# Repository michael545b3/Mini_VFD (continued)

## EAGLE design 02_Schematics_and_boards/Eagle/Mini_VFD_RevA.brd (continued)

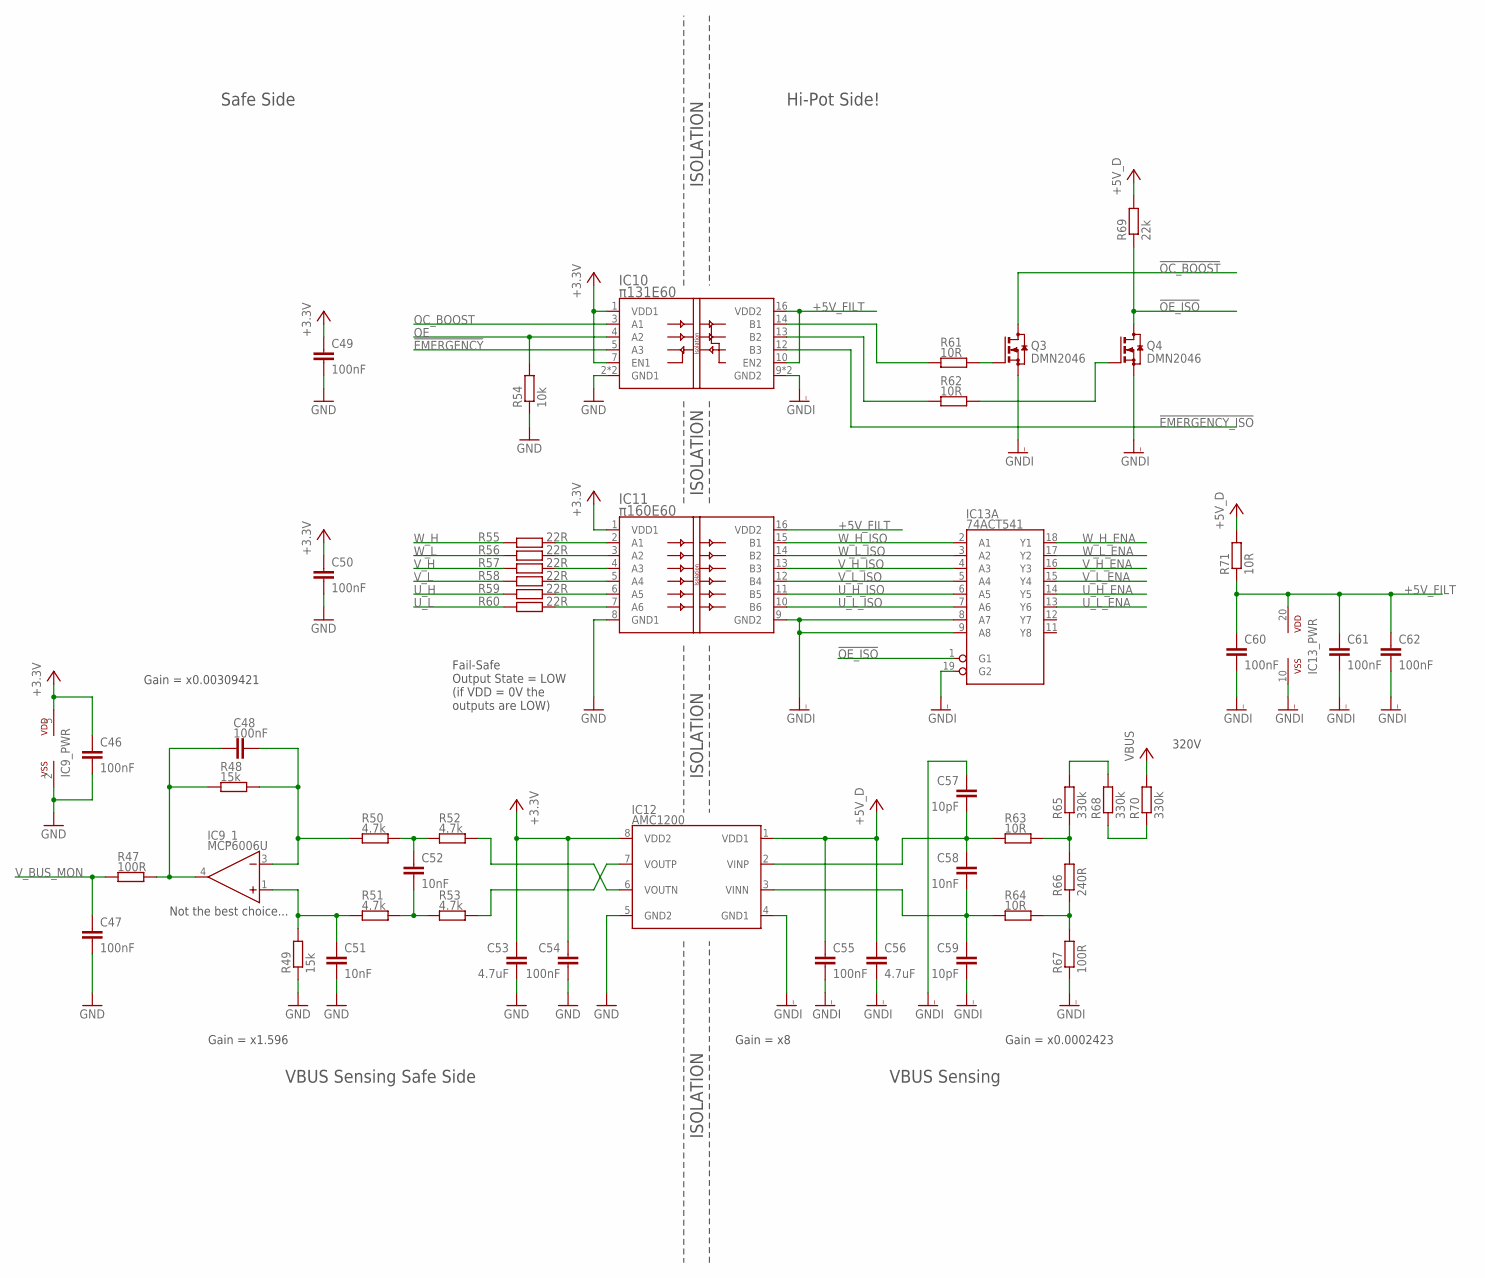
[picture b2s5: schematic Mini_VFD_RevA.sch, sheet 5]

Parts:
C46, C47, C48, C49, C50, C54, C55, C60, C61, C62: 100nF; C0603
C51, C52, C58: 10nF; C0603
C53, C56: 4.7uF; C0603
C57, C59: 10pF; C0603
IC9: MCP6006U; SOT23-5
IC10: π131E60; SOIC16R
IC11: π160E60; SOIC16R
IC12: AMC1200; SOIC8_W
IC13: 74ACT541; SOIC20NS
Q3, Q4: DMN2046; SOT23
R47, R67: 100R; R0603
R48, R49: 15k; R0603
R50, R51, R52, R53: 4.7k; R0603
R54: 10k; R0603
R55, R56, R57, R58, R59, R60: 22R; R0603
R61, R62, R63, R64, R71: 10R; R0603
R65, R68, R70: 330k; R1206
R66: 240R; R0603
R69: 22k; R0603

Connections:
!EMERGENCY: IC10.5 (A3); also elsewhere on the board
!EMERGENCY_ISO: IC10.12 (B3); also elsewhere on the board
!OC_BOOST: Q3.3 (D); also elsewhere on the board
!OE_ISO: IC13.1 (G1), Q4.3 (D), R69.1
+3.3V: C46.1, C49.1, C50.1, C53.1, C54.1, IC9.5 (VDD), IC10.1 (VDD1), IC10.7 (EN1), IC11.1 (VDD1), IC12.8 (VDD2); also elsewhere on the board
+5V_D: C55.1, C56.1, IC12.1 (VDD1), R69.2, R71.2; also elsewhere on the board
+5V_FILT: C60.1, C61.1, C62.1, IC10.10 (EN2), IC10.16 (VDD2), IC11.16 (VDD2), IC13.20 (VDD), R71.1
GND: C46.2, C47.2, C49.2, C50.2, C51.2, C53.2, C54.2, IC9.2 (VSS), IC10.2 (GND1), IC10.8 (GND1), IC11.8 (GND1), IC12.5 (GND2), R49.1, R54.1; also elsewhere on the board
GNDI: C55.2, C56.2, C57.1, C59.2, C60.2, C61.2, C62.2, IC10.9 (GND2), IC10.15 (GND2), IC11.9 (GND2), IC12.4 (GND1), IC13.8 (A7), IC13.9 (A8), IC13.10 (VSS), IC13.19 (G2), Q3.2 (S), Q4.2 (S), R67.1; also elsewhere on the board
unnamed: Q3.1 (G), R61.2
unnamed: IC12.6 (VOUTN), R52.1
unnamed: IC11.2 (A1), R55.2
unnamed: IC11.3 (A2), R56.2
unnamed: IC11.4 (A3), R57.2
unnamed: IC10.14 (B1), R61.1
unnamed: R64.1, R66.1, R67.2
unnamed: IC11.5 (A4), R58.2
unnamed: IC10.13 (B2), R62.1
unnamed: IC11.6 (A5), R59.2
unnamed: IC11.7 (A6), R60.2
unnamed: Q4.1 (G), R62.2
unnamed: R68.1, R70.1
unnamed: R65.2, R68.2
unnamed: IC12.7 (VOUTP), R53.1
unnamed: C52.1, R50.1, R52.2
unnamed: C52.2, R51.1, R53.2
unnamed: C48.2, IC9.3 (-IN), R48.1, R50.2
unnamed: C51.1, IC9.1 (+IN), R49.2, R51.2
unnamed: C48.1, IC9.4 (OUT), R47.1, R48.2
OC_BOOST: IC10.3 (A1); also elsewhere on the board
OE: IC10.4 (A2), R54.2; also elsewhere on the board
U_H: R59.1; also elsewhere on the board
U_H_ENA: IC13.14 (Y5); also elsewhere on the board
U_H_ISO: IC11.11 (B5), IC13.6 (A5)
U_L: R60.1; also elsewhere on the board
U_L_ENA: IC13.13 (Y6); also elsewhere on the board
U_L_ISO: IC11.10 (B6), IC13.7 (A6)
VBUS: R70.2; also elsewhere on the board
VBUS_MON: C57.2, C58.1, IC12.2 (VINP), R63.2
VBUS_MON_ATT: R63.1, R65.1, R66.2
VBUS_MON_NEG: C58.2, C59.1, IC12.3 (VINN), R64.2
V_BUS_MON: C47.1, R47.2; also elsewhere on the board
V_H: R57.1; also elsewhere on the board
V_H_ENA: IC13.16 (Y3); also elsewhere on the board
V_H_ISO: IC11.13 (B3), IC13.4 (A3)
V_L: R58.1; also elsewhere on the board
V_L_ENA: IC13.15 (Y4); also elsewhere on the board
V_L_ISO: IC11.12 (B4), IC13.5 (A4)
W_H: R55.1; also elsewhere on the board
W_H_ENA: IC13.18 (Y1); also elsewhere on the board
W_H_ISO: IC11.15 (B1), IC13.2 (A1)
W_L: R56.1; also elsewhere on the board
W_L_ENA: IC13.17 (Y2); also elsewhere on the board
W_L_ISO: IC11.14 (B2), IC13.3 (A2)

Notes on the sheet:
Fail-Safe Output State = LOW (if VDD = 0V the outputs are LOW)
ISOLATION
Gain = x8
320V
Gain = x0.0002423
Safe Side
Hi-Pot Side!
VBUS Sensing
VBUS Sensing Safe Side
Not the best choice...
Gain = x1.596
Gain = x0.00309421

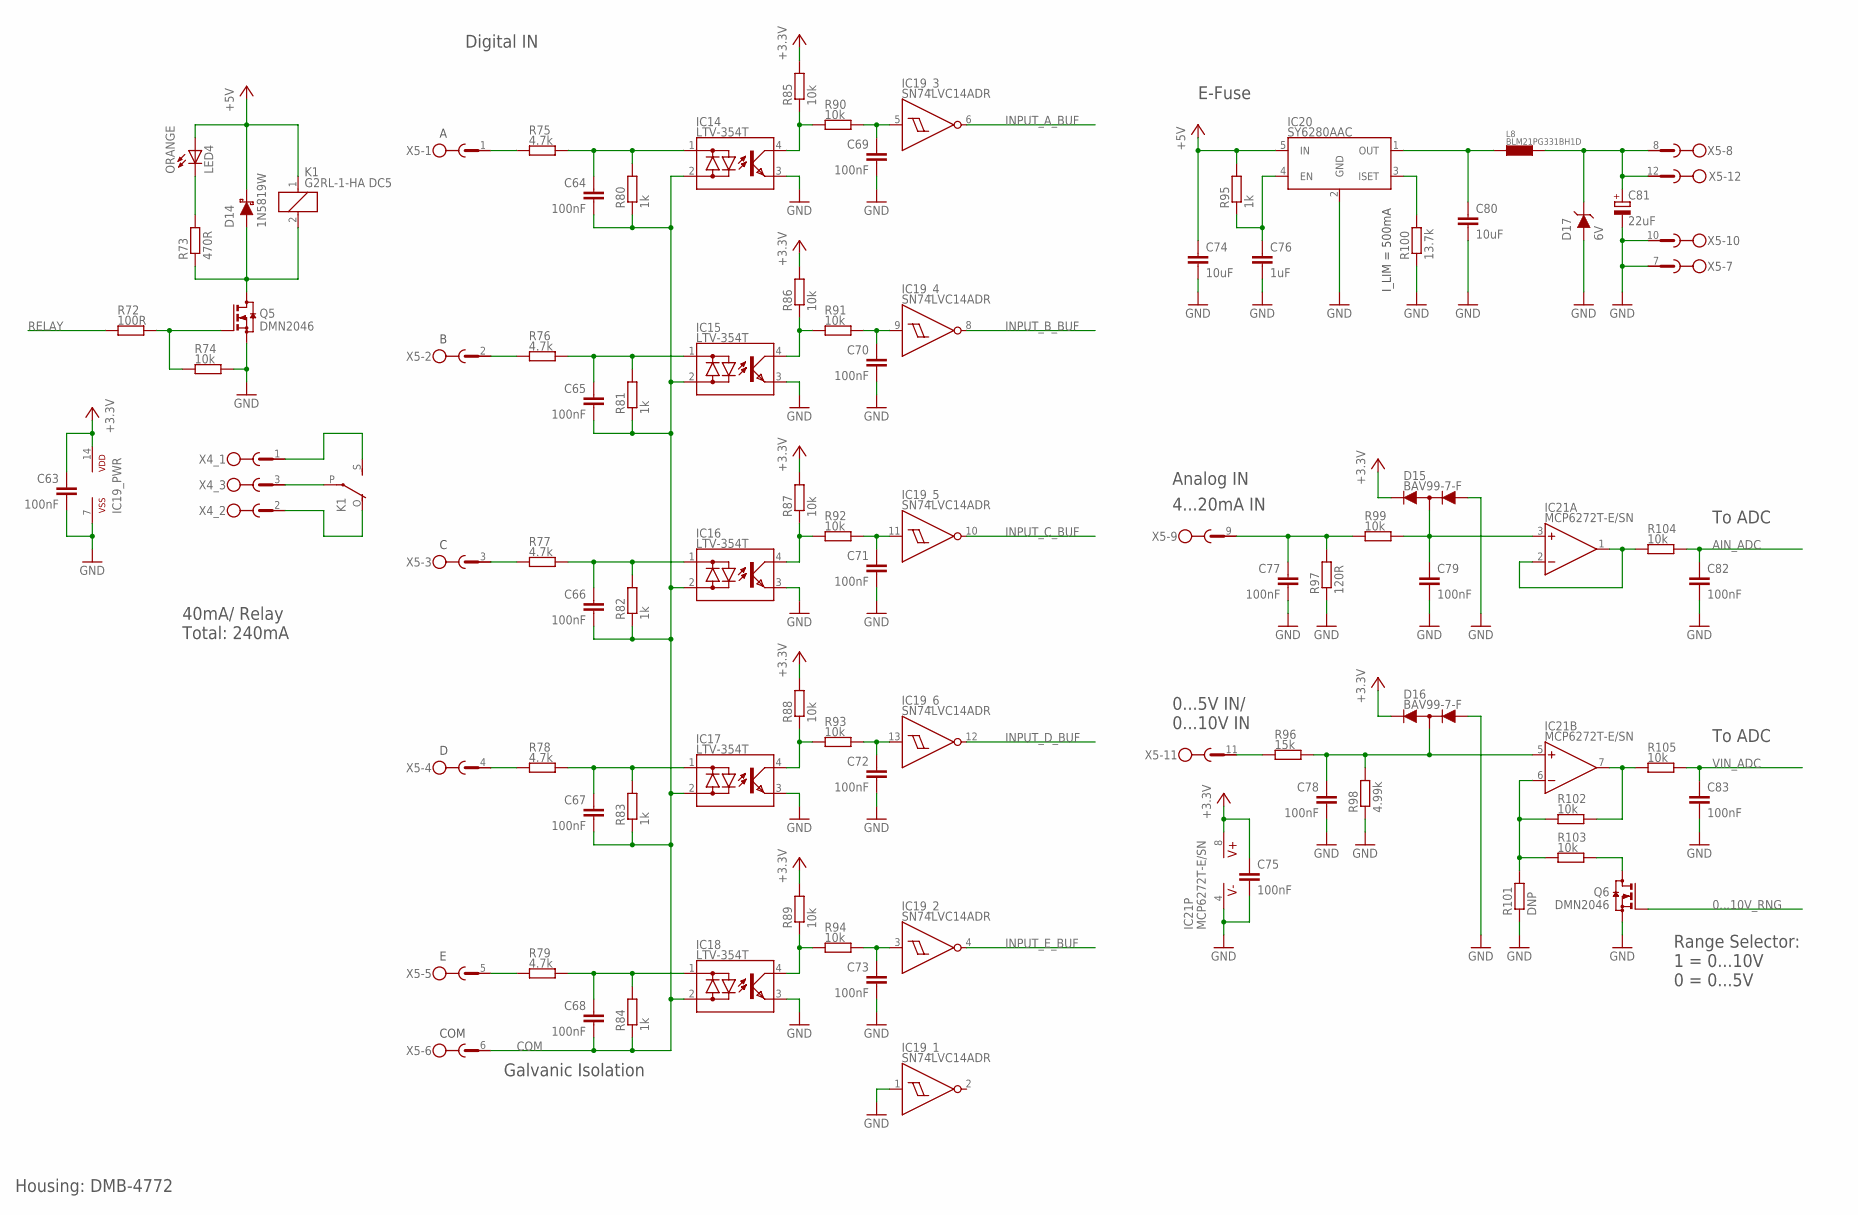
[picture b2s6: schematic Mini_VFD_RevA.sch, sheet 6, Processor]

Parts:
C63, C64, C65, C66, C67, C68, C69, C70, C71, C72, C73, C75, C77, C78, C79, C82, C83: 100nF; C0603
C74, C80: 10uF; C0805
C76: 1uF; C0603
C81: 22uF; E2-5
D14: 1N5819W; SOD123
D15, D16: BAV99-7-F; SOT23
D17: 6V; DO214AC
IC14, IC15, IC16, IC17, IC18: LTV-354T; SOP04
IC19: SN74LVC14ADR; SO14
IC20: SY6280AAC; SOT23-5
IC21: MCP6272T-E/SN; SO08
K1: G2RL-1-HA DC5; E3206S
L8: BLM21PG331BH1D; R0805
LED4: ORANGE; LED_0603
Q5, Q6: DMN2046; SOT23
R72: 100R; R0603
R73: 470R; R0603
R74, R85, R86, R87, R88, R89, R90, R91, R92, R93, R94, R99, R102, R103, R104, R105: 10k; R0603
R75, R76, R77, R78, R79: 4.7k; R0805
R80, R81, R82, R83, R84, R95: 1k; R0603
R96: 15k; R0603
R97: 120R; R1206
R98: 4.99k; R0603
R100: 13.7k; R0603
R101: DNP; R0603
X4: MSTBV3
X5: MSTBV12

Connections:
0...10V_RNG: Q6.1 (G); also elsewhere on the board
!INPUT_A: IC14.4 (C), R85.1, R90.1
!INPUT_A_FILT: C69.1, IC19.5 (I), R90.2
!INPUT_B: IC15.4 (C), R86.1, R91.1
!INPUT_B_FILT: C70.1, IC19.9 (I), R91.2
!INPUT_C: IC16.4 (C), R87.1, R92.1
!INPUT_C_FILT: C71.1, IC19.11 (I), R92.2
!INPUT_D: IC17.4 (C), R88.1, R93.1
!INPUT_D_FILT: C72.1, IC19.13 (I), R93.2
!INPUT_E: IC18.4 (C), R89.1, R94.1
!INPUT_E_FILT: C73.1, IC19.3 (I), R94.2
+3.3V: C63.1, C75.1, D15.2 (C), D16.2 (C), IC19.14 (VDD), IC21.8 (V+), R85.2, R86.2, R87.2, R88.2, R89.2; also elsewhere on the board
+5V: C74.1, D14.1 (C), IC20.5 (IN), K1.1, LED4.A, R95.2; also elsewhere on the board
+5V_OUT: C81.+, D17.C, L8.2, X5.8, X5.12
AIN_ADC: C82.1, R104.2; also elsewhere on the board
COM: C64.2, C65.2, C66.2, C67.2, C68.2, IC14.2 (AC2), IC15.2 (AC2), IC16.2 (AC2), IC17.2 (AC2), IC18.2 (AC2), R80.1, R81.1, R82.1, R83.1, R84.1, X5.6
GND: C63.2, C69.2, C70.2, C71.2, C72.2, C73.2, C74.2, C75.2, C76.2, C77.2, C78.2, C79.2, C80.2, C81.-, C82.2, C83.2, D15.1 (A), D16.1 (A), D17.A, IC14.3 (E), IC15.3 (E), IC16.3 (E), IC17.3 (E), IC18.3 (E), IC19.1 (I), IC19.7 (VSS), IC20.2 (GND), IC21.4 (V-), Q5.2 (S), Q6.2 (S), R74.2, R97.1, R98.1, R100.1, R101.1, X5.7, X5.10; also elsewhere on the board
INPUT_A_BUF: IC19.6 (O); also elsewhere on the board
INPUT_B_BUF: IC19.8 (O); also elsewhere on the board
INPUT_C_BUF: IC19.10 (O); also elsewhere on the board
INPUT_D_BUF: IC19.12 (O); also elsewhere on the board
INPUT_E_BUF: IC19.4 (O); also elsewhere on the board
IN_A: R75.1, X5.1
IN_A_OPTO: C64.1, IC14.1 (AC1), R75.2, R80.2
IN_B: R76.1, X5.2
IN_B_OPTO: C65.1, IC15.1 (AC1), R76.2, R81.2
IN_C: R77.1, X5.3
IN_C_OPTO: C66.1, IC16.1 (AC1), R77.2, R82.2
IN_D: R78.1, X5.4
IN_D_OPTO: C67.1, IC17.1 (AC1), R78.2, R83.2
IN_E: R79.1, X5.5
IN_E_OPTO: C68.1, IC18.1 (AC1), R79.2, R84.2
unnamed: LED4.C, R73.2
unnamed: C77.1, R97.2, R99.1, X5.9
unnamed: IC20.3 (ISET), R100.2
unnamed: C79.1, D15.3 (AC), IC21.3 (+IN), R99.2
unnamed: C76.1, IC20.4 (EN), R95.1
unnamed: IC21.1 (OUT), IC21.2 (-IN), R104.1
unnamed: C78.1, D16.3 (AC), IC21.5 (+IN), R96.2, R98.2
unnamed: R96.1, X5.11
unnamed: IC21.7 (OUT), R102.2, R105.1
unnamed: IC21.6 (-IN), R101.2, R102.1, R103.2
unnamed: Q6.3 (D), R103.1
unnamed: C80.1, IC20.1 (OUT), L8.1
unnamed: K1.P, X4.3
unnamed: K1.O, X4.2
unnamed: K1.S, X4.1
RELAY: R72.1; also elsewhere on the board
RELAY_DRAIN: D14.2 (A), K1.2, Q5.3 (D), R73.1
RELAY_R: Q5.1 (G), R72.2, R74.1
VIN_ADC: C83.1, R105.2; also elsewhere on the board

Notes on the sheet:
Housing: DMB-4772
40mA/ Relay Total: 240mA
I_LIM = 500mA
COM
Digital IN
Analog IN
4...20mA IN
0...5V IN/ 0...10V IN
Range Selector: 1 = 0...10V 0 = 0...5V
To ADC
Galvanic Isolation
E-Fuse

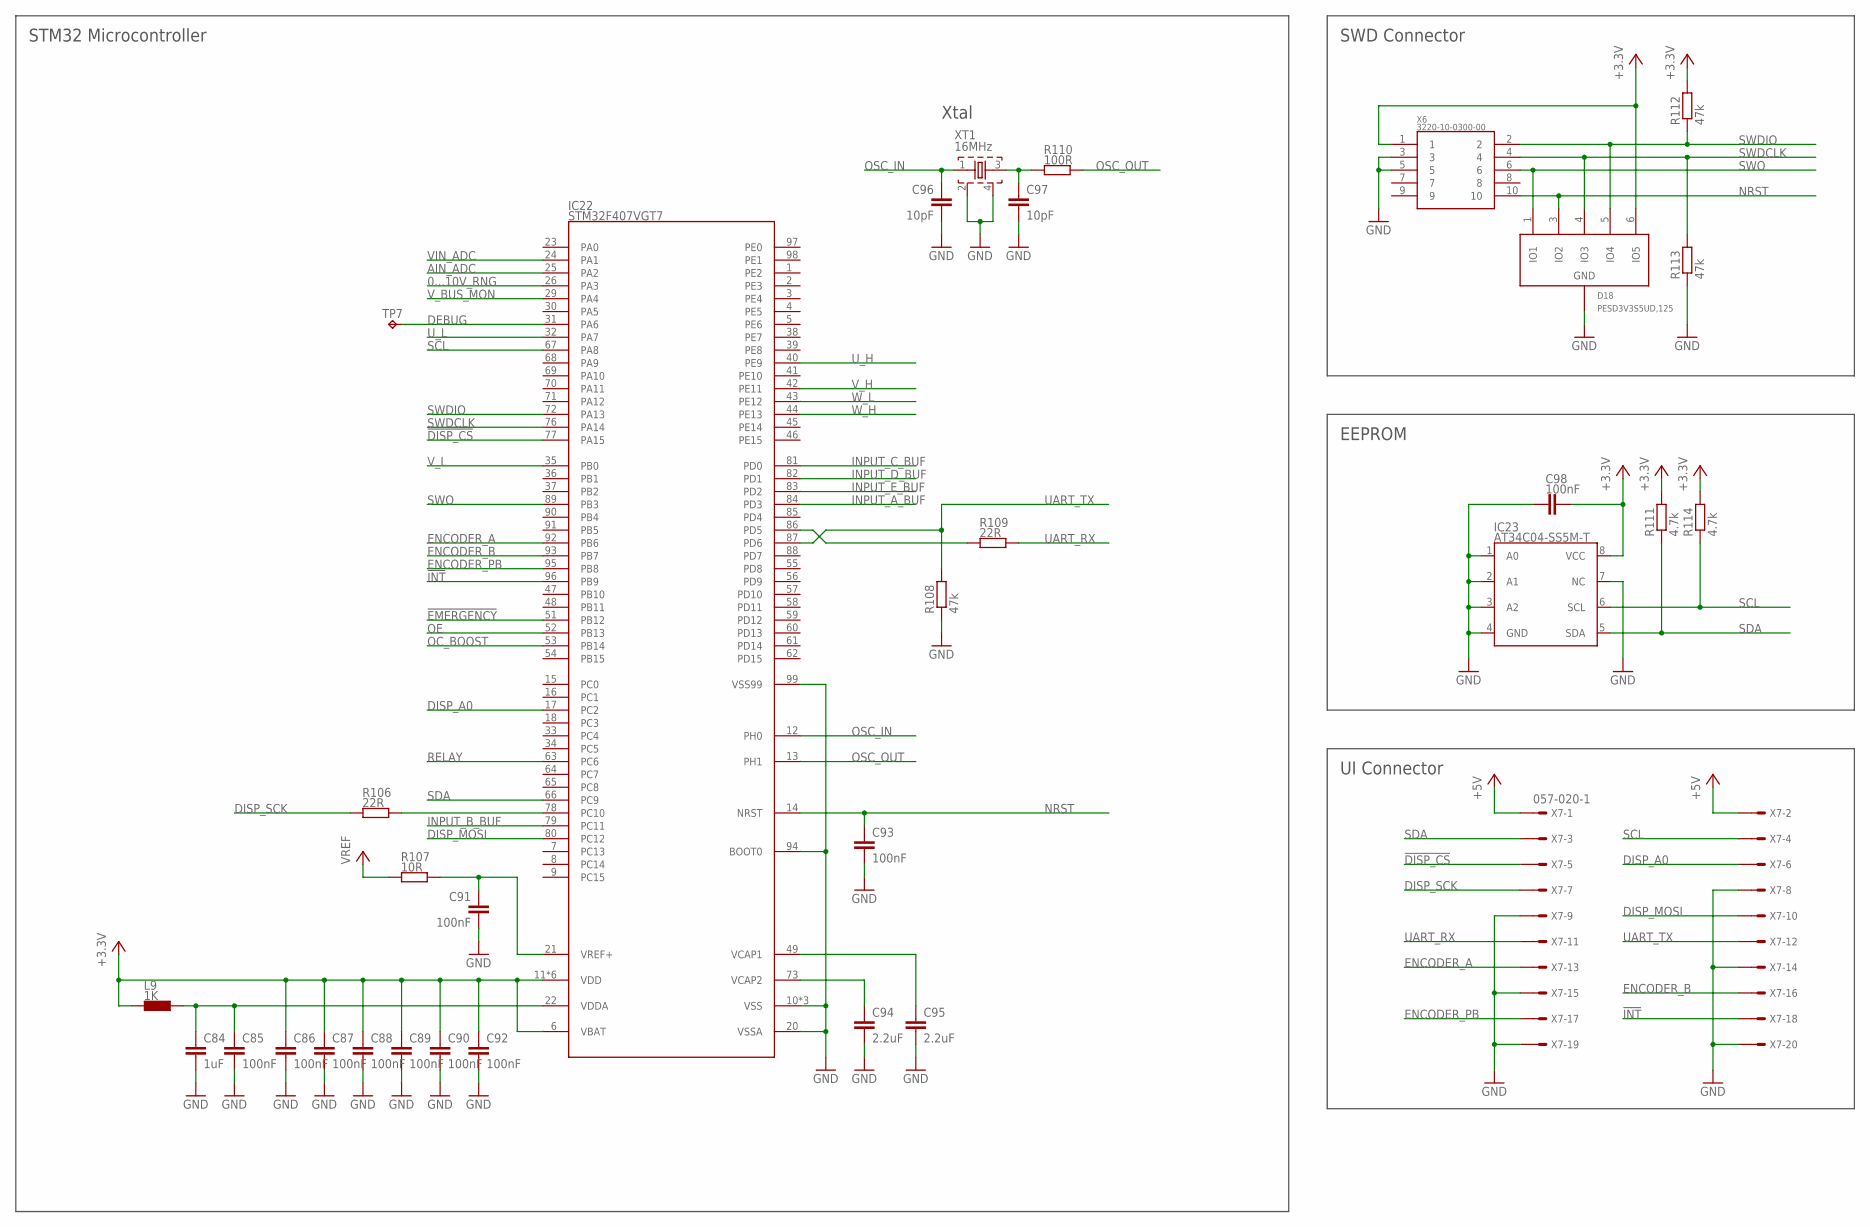
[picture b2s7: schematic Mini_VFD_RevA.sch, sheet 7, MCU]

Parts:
C84: 1uF; C0603
C85, C86, C87, C88, C89, C90, C91, C92, C93, C98: 100nF; C0603
C94, C95: 2.2uF; C0603
C96, C97: 10pF; C0603
D18: PESD3V3S5UD,125; TSOP-6
IC22: STM32F407VGT7; LQFP100
IC23: AT34C04-SS5M-T; SOIC8
L9: 1K; R0603
R106, R109: 22R; R0603
R107: 10R; R0603
R108, R112, R113: 47k; R0603
R110: 100R; R0603
R111, R114: 4.7k; R0603
TP7: TP_SOLDREYE; SOLDER_EYE
X6: 3220-10-0300-00
X7: 057-020-1
XT1: 16MHz; 3225_4P

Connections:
0...10V_RNG: IC22.26 (PA3); also elsewhere on the board
!DISP_CS: IC22.77 (PA15), X7.5
!EMERGENCY: IC22.51 (PB12); also elsewhere on the board
!INT: IC22.96 (PB9), X7.18
+3.3V: C86.1, C87.1, C88.1, C89.1, C90.1, C92.1, C98.2, D18.6 (IO5), IC22.6 (VBAT), IC22.11 (VDD), IC22.19 (VDD), IC22.28 (VDD), IC22.50 (VDD), IC22.75 (VDD), IC22.100 (VDD), IC23.8 (VCC), L9.2, R111.2, R112.2, R114.2, X6.1; also elsewhere on the board
+3.3V_FILT: C84.1, C85.1, IC22.22 (VDDA), L9.1
+5V: X7.1, X7.2; also elsewhere on the board
AIN_ADC: IC22.25 (PA2); also elsewhere on the board
DEBUG: IC22.31 (PA6), TP7.1
DISP_A0: IC22.17 (PC2), X7.6
DISP_MOSI: IC22.80 (PC12), X7.10
DISP_SCK: R106.1, X7.7
ENCODER_A: IC22.92 (PB6), X7.13
ENCODER_B: IC22.93 (PB7), X7.16
ENCODER_PB: IC22.95 (PB8), X7.17
GND: C84.2, C85.2, C86.2, C87.2, C88.2, C89.2, C90.2, C91.2, C92.2, C93.2, C94.2, C95.2, C96.2, C97.2, C98.1, D18.2 (GND), IC22.10 (VSS), IC22.20 (VSSA), IC22.27 (VSS), IC22.74 (VSS), IC22.94 (BOOT0), IC22.99 (VSS99), IC23.1 (A0), IC23.2 (A1), IC23.3 (A2), IC23.4 (GND), IC23.7 (NC), R108.1, R113.1, X6.3, X6.5, X7.8, X7.9, X7.14, X7.15, X7.19, X7.20, XT1.2, XT1.4; also elsewhere on the board
INPUT_A_BUF: IC22.84 (PD3); also elsewhere on the board
INPUT_B_BUF: IC22.79 (PC11); also elsewhere on the board
INPUT_C_BUF: IC22.81 (PD0); also elsewhere on the board
INPUT_D_BUF: IC22.82 (PD1); also elsewhere on the board
INPUT_E_BUF: IC22.83 (PD2); also elsewhere on the board
unnamed: IC22.78 (PC10), R106.2
unnamed: IC22.86 (PD5), R109.1
unnamed: C94.1, IC22.73 (VCAP2)
unnamed: C95.1, IC22.49 (VCAP1)
unnamed: C97.1, R110.1, XT1.3
unnamed: C91.1, IC22.21 (VREF+), R107.2
NRST: C93.1, D18.3 (IO2), IC22.14 (NRST), X6.10
OC_BOOST: IC22.53 (PB14); also elsewhere on the board
OE: IC22.52 (PB13); also elsewhere on the board
OSC_IN: C96.1, IC22.12 (PH0), XT1.1
OSC_OUT: IC22.13 (PH1), R110.2
RELAY: IC22.63 (PC6); also elsewhere on the board
SCL: IC22.67 (PA8), IC23.6 (SCL), R114.1, X7.4
SDA: IC22.66 (PC9), IC23.5 (SDA), R111.1, X7.3
SWDCLK: D18.4 (IO3), IC22.76 (PA14), R113.2, X6.4
SWDIO: D18.5 (IO4), IC22.72 (PA13), R112.1, X6.2
SWO: D18.1 (IO1), IC22.89 (PB3), X6.6
UART_RX: R109.2, X7.11
UART_TX: IC22.87 (PD6), R108.2, X7.12
U_H: IC22.40 (PE9); also elsewhere on the board
U_L: IC22.32 (PA7); also elsewhere on the board
VIN_ADC: IC22.24 (PA1); also elsewhere on the board
VREF: R107.1; also elsewhere on the board
V_BUS_MON: IC22.29 (PA4); also elsewhere on the board
V_H: IC22.42 (PE11); also elsewhere on the board
V_L: IC22.35 (PB0); also elsewhere on the board
W_H: IC22.44 (PE13); also elsewhere on the board
W_L: IC22.43 (PE12); also elsewhere on the board

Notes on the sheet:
SWD Connector
STM32 Microcontroller
UI Connector
EEPROM
Xtal

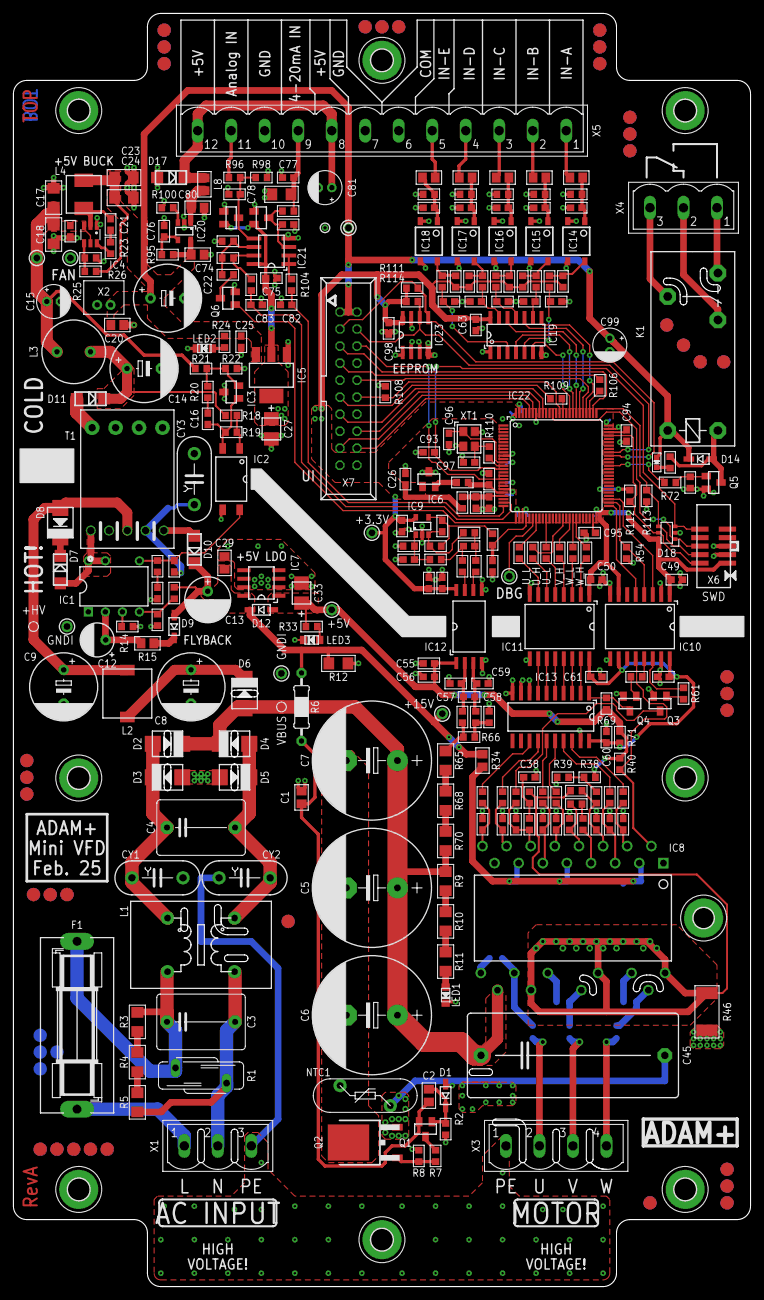
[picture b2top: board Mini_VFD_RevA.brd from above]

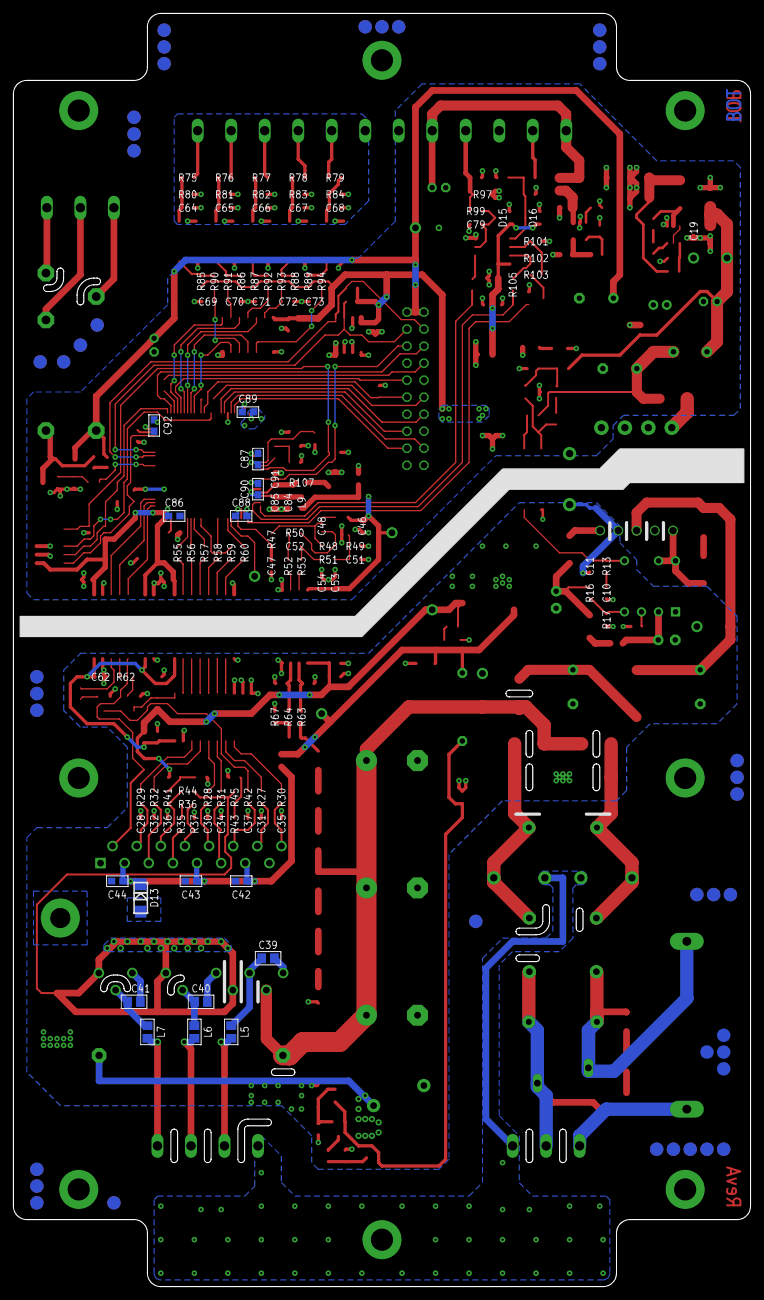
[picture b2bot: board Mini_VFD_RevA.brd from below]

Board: 2 copper layers, 110.0 x 190.0 mm, 308 parts (16 on the bottom side), 195 nets.

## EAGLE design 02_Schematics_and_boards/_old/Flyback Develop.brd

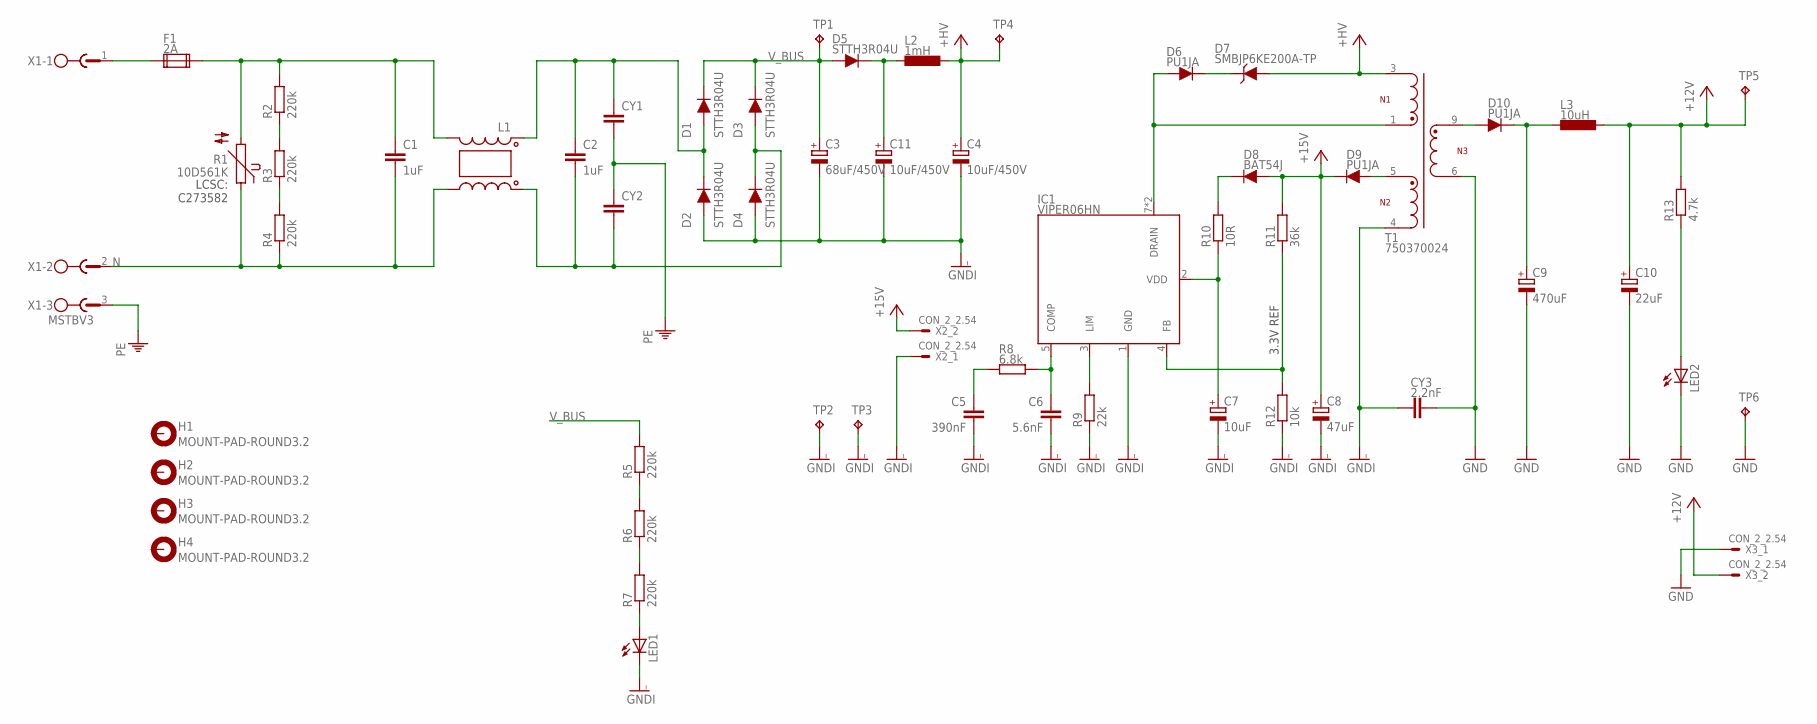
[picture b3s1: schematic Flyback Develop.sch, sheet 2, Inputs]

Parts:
C1, C2: 1uF; C102-082X133
C3: 68uF/450V; E7,5-18
C4, C11: 10uF/450V; E3,5-10
C5: 390nF; C0603
C6: 5.6nF; C0603
C7: 10uF; E2,5-5
C8: 47uF; E2,5-7
C9: 470uF; E3,5-8
C10: 22uF; E2-5
CY1, CY2: CYYC7B5; YC7B5
CY3: 2.2nF; YC7B5
D1, D2, D3, D4, D5: STTH3R04U; SMB
D6, D9, D10: PU1JA; DO214AC
D7: SMBJP6KE200A-TP; DO214AC
D8: BAT54J; SOD123
F1: 2A; 2010-FUSE
H1, H2, H3, H4: MOUNT-PAD-ROUND3.2; 3,2-PAD
IC1: VIPER06HN; DIL07
L1: 20mH; CMC_SLT
L2: 1mH; SLH0704
L3: 10uH; COIL_4X4
LED1, LED2: LED_0805
R1: 10D561K; S10K175
R2, R3, R4, R5, R6, R7: 220k; R1210
R8: 6.8k; R0603
R9: 22k; R0603
R10: 10R; R0805
R11: 36k; R0603
R12: 10k; R0603
R13: 4.7k; R0603
T1: 750370024; WE-OLSTM_EE13_L13.72W20.45H10.8
TP1, TP2, TP3, TP4, TP5, TP6: TP_SOLDREYE; SOLDER_EYE
X1: MSTBV3
X2, X3: CON_2_2.54; 1X02

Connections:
+12V: C10.+, L3.1, R13.2, TP5.1, X3.2
+15V: C8.+, D8.2 (A), D9.C, R11.2, X2.2
+HV: C4.+, D7.A, L2.1, T1.3, TP4.1
GND: C9.-, C10.-, CY3.2, LED2.C, T1.6, TP6.1, X3.1
GNDI: C3.-, C4.-, C5.2, C6.2, C7.-, C8.-, C11.-, CY3.1, D2.A, D4.A, IC1.1 (GND), LED1.C, R9.1, R12.1, T1.4, TP2.1, TP3.1, X2.1
L': C1.1, F1.P$2 (2), L1.OUT1, R1.2, R2.2
N: C1.2, L1.OUT2, R1.1, R4.1, X1.2
unnamed: D6.C, D7.C
unnamed: R5.1, R6.2
unnamed: R6.1, R7.2
unnamed: LED1.A, R7.1
unnamed: C9.+, D10.C, L3.2
unnamed: LED2.A, R13.1
unnamed: C11.+, D5.C, L2.2
unnamed: C2.2, CY2.2, D3.A, D4.C, L1.IN2
unnamed: F1.P$1 (1), X1.1
unnamed: R2.1, R3.2
unnamed: R3.1, R4.2
unnamed: D10.A, T1.9
unnamed: D6.A, IC1.7 (DRAIN), IC1.8 (DRAIN), T1.1
unnamed: C5.1, R8.1
unnamed: D8.1 (C), R10.2
unnamed: C7.+, IC1.2 (VDD), R10.1
unnamed: IC1.3 (LIM), R9.2
unnamed: D9.A, T1.5
unnamed: IC1.4 (FB), R11.1, R12.2
unnamed: C6.1, IC1.5 (COMP), R8.2
unnamed: C2.1, CY1.1, D1.A, D2.C, L1.IN1
PE: CY1.2, CY2.1, X1.3
V_BUS: C3.+, D1.C, D3.C, D5.A, R5.2, TP1.1

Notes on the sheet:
LCSC: C273582
3.3V REF

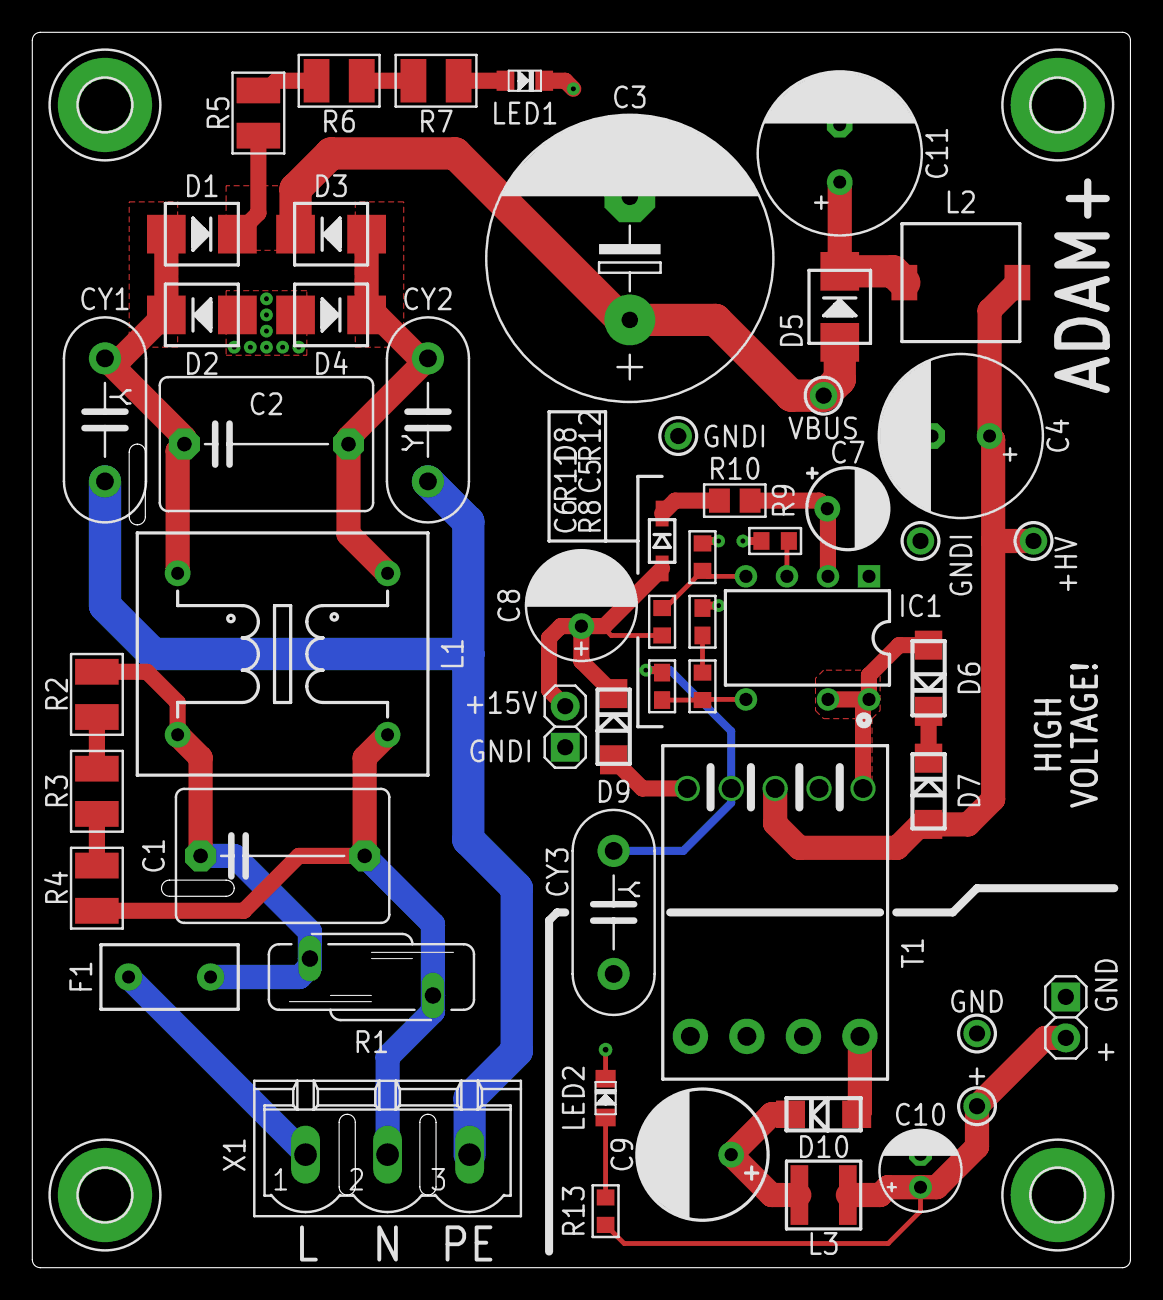
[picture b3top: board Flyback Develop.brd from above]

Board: 2 copper layers, 68.0 x 76.5 mm, 58 parts (0 on the bottom side), 30 nets.

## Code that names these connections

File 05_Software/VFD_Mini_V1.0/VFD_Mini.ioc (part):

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Mcu.Name=STM32F407V(E-G)Tx
Mcu.Package=LQFP100
Mcu.UserName=STM32F407VETx
PA1.GPIOParameters=GPIO_Label
PA1.GPIO_Label=V_ADC
PA1.Signal=ADCx_IN1
PA13.Mode=Trace_Asynchronous_SW
PA13.Signal=SYS_JTMS-SWDIO
PA14.Mode=Trace_Asynchronous_SW
PA14.Signal=SYS_JTCK-SWCLK
PA15.GPIOParameters=GPIO_Label
PA15.GPIO_Label=SPI_CS
PA15.Signal=GPIO_Output
PA2.GPIOParameters=GPIO_Label
PA2.GPIO_Label=MA_ADC
PA2.Signal=ADCx_IN2
PA3.GPIOParameters=GPIO_Label
PA3.GPIO_Label=IN_RANGE
PA3.Signal=GPIO_Output
PA4.GPIOParameters=GPIO_Label
PA4.GPIO_Label=V_BUS_MON
PA4.Signal=ADCx_IN4
PA6.GPIOParameters=GPIO_Label
PA6.GPIO_Label=DEBUG
PA6.Signal=GPIO_Output
PA7.Mode=PWM Generation1 CH1 CH1N
PA7.Signal=TIM1_CH1N
PA8.Mode=I2C
PA8.Signal=I2C3_SCL
PB0.Mode=PWM Generation2 CH2 CH2N
PB0.Signal=TIM1_CH2N
PB12.GPIOParameters=GPIO_Label
PB12.GPIO_Label=EMERGENCY
PB12.Signal=GPIO_Input
PB13.GPIOParameters=GPIO_Label
PB13.GPIO_Label=OE
PB13.Signal=GPIO_Output
PB14.GPIOParameters=GPIO_Label
PB14.GPIO_Label=OC_BOOST
PB14.Signal=GPIO_Output
PB3.Mode=Trace_Asynchronous_SW
PB3.Signal=SYS_JTDO-SWO
PB6.Signal=S_TIM4_CH1
PB7.Signal=S_TIM4_CH2
PB8.GPIOParameters=GPIO_Label
PB8.GPIO_Label=ENCODER_PB
PB8.Signal=GPIO_Input
PB9.GPIOParameters=GPIO_Label
PB9.GPIO_Label=INT_N
PB9.Signal=GPIO_Input
PC10.Mode=TX_Only_Simplex_Unidirect_Master
PC10.Signal=SPI3_SCK
PC11.GPIOParameters=GPIO_Label
PC11.GPIO_Label=INPUT_B_BUF
PC11.Signal=GPIO_Input
PC12.Mode=TX_Only_Simplex_Unidirect_Master
PC12.Signal=SPI3_MOSI
PC2.GPIOParameters=GPIO_Label
PC2.GPIO_Label=DISP_RS
PC2.Signal=GPIO_Output
PC6.GPIOParameters=GPIO_Label
PC6.GPIO_Label=RELAY
PC6.Signal=GPIO_Output
PC9.Mode=I2C
PC9.Signal=I2C3_SDA
PD0.GPIOParameters=GPIO_Label
PD0.GPIO_Label=INPUT_C_BUF
PD0.Signal=GPIO_Input
PD1.GPIOParameters=GPIO_Label
PD1.GPIO_Label=INPUT_D_BUF
PD1.Signal=GPIO_Input
PD2.GPIOParameters=GPIO_Label
PD2.GPIO_Label=INPUT_E_BUF
PD2.Signal=GPIO_Input
PD3.GPIOParameters=GPIO_Label
PD3.GPIO_Label=INPUT_A_BUF
PD3.Signal=GPIO_Input
PD5.Mode=Asynchronous
PD5.Signal=USART2_TX
PD6.Mode=Asynchronous
PD6.Signal=USART2_RX
PE11.Signal=S_TIM1_CH2
PE12.Mode=PWM Generation3 CH3 CH3N
PE12.Signal=TIM1_CH3N
PE13.Signal=S_TIM1_CH3
PE9.Signal=S_TIM1_CH1
PH0-OSC_IN.Mode=HSE-External-Oscillator
PH0-OSC_IN.Signal=RCC_OSC_IN
PH1-OSC_OUT.Mode=HSE-External-Oscillator
PH1-OSC_OUT.Signal=RCC_OSC_OUT
RCC.HSE_VALUE=16000000
RCC.SYSCLKFreq_VALUE=168000000
RCC.SYSCLKSource=RCC_SYSCLKSOURCE_PLLCLK
board=custom

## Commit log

2025-07-06 Init Commit
2025-07-06 Added Pictures
2025-07-06 Added Software
2025-07-06 Edited Pictures
2025-07-06 Rename IMG_20250705_084131_701.jpg to Mini_VFD_Top_View
2025-07-06 Created README.md
2025-07-06 Created Gitignore
2025-07-08 Edited Documentation
